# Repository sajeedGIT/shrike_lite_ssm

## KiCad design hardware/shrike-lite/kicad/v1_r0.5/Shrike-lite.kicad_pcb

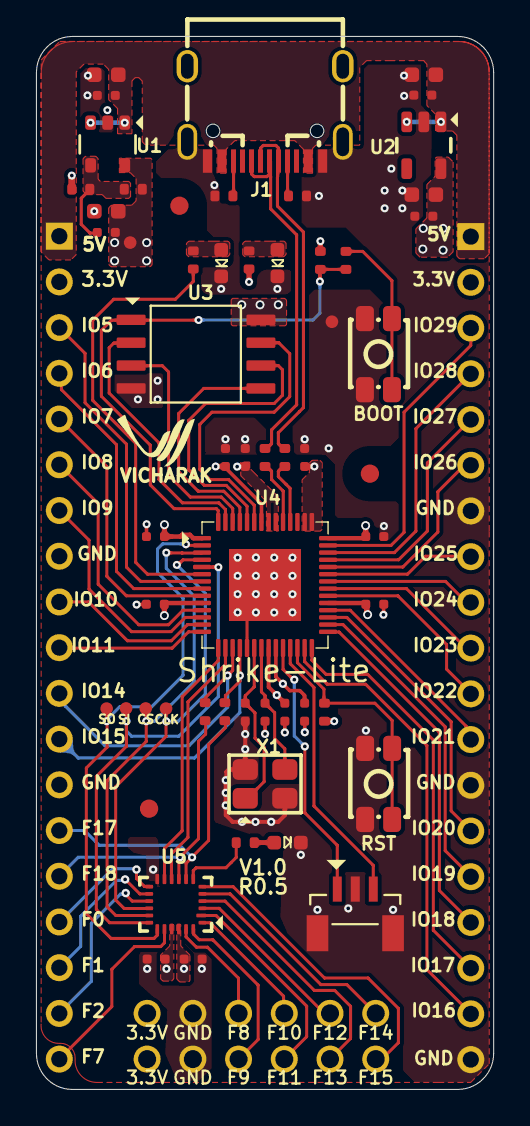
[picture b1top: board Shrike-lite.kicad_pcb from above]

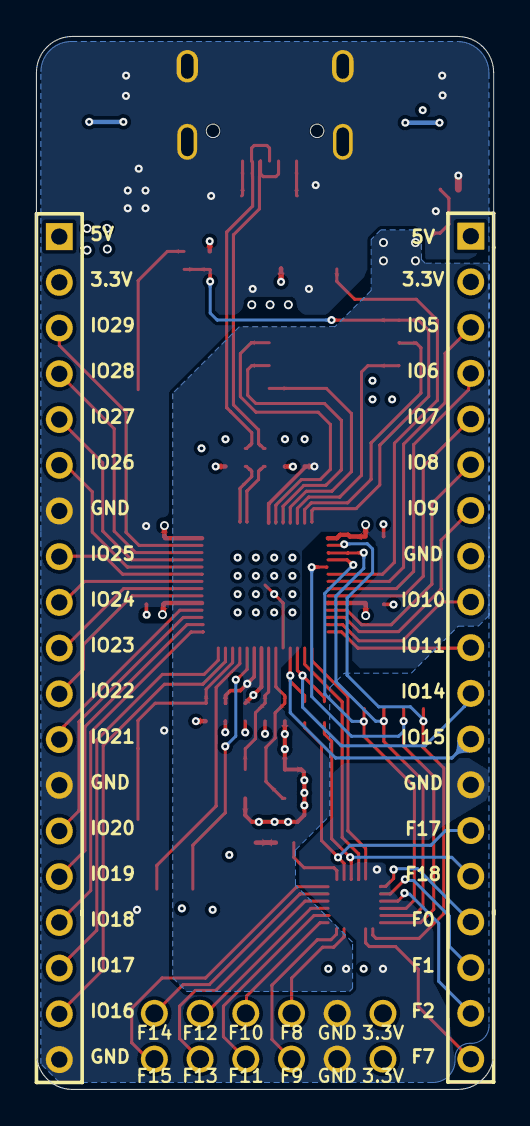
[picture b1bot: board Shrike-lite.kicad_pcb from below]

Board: 4 copper layers, 25.4 x 58.5 mm, 57 parts (2 on the bottom side), 71 nets.

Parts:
2: TP
C1, C3, C5, C8: 100nF 10V; Cap_0603
C2, C4, C6, C7, C9, C10, C11, C12, C13, C14, C15, C16, C17, C18, C19, C20, C21: Cap_0402
CLK: TP
CS: TP
D1: LED1; LED_0603
D2, D3: LED_0603
GND1: TP
J1: Type-C
J2, J4: Header 19X1_2.54MM; 1X19_HEADER
J3: DNP; 2X6_HEADER
J5: XUNPU WAFER-SH1.0-3PLB
R1: RES_0402_5; Res_0402
R2, R3, R4, R5, R6, R7, R8, R9, R10, R11, R12, R13, R14: Res_0402
SI: TP
SO: TP
SW1: SW PUSHBUTTON; SW_MICRO PUSH BUTTON 4 PAD
SW2: SW PUSHBUTTON; Switch
U1: SOT23-5
U2: SOT25
U3: SOIC-8
U4: RP2040; QFN_56
U5: QFN_24
X1: CRYSTAL_3225

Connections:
1.1V: 2.1, C7.2, C8.2, C11.1, C12.1, C20.1, R4.1, U1.5, U4.23, U4.50, U5.22
3.3V: C3.2, C4.2, C13.1, C14.1, C15.1, C16.1, C17.1, C18.1, C19.1, C21.1, J2.2, J3.1, J3.2, J4.2, R1.1, R9.1, R10.2, U2.5, U3.8, U4.1, U4.10, U4.22, U4.33, U4.42, U4.43, U4.44, U4.48, U4.49, U5.21
BOOT: R11.2, SW2.1, SW2.2
CS0: R9.2, R11.1, U3.1, U4.56
CS1: CS.1, U4.3, U5.17
EN: U4.16, U5.10
F_GPIO0: J2.16, U5.13
F_GPIO1: J2.17, U5.14
F_GPIO2: J2.18, U5.15
F_GPIO7: J2.19, U5.20
F_GPIO8: J3.6, U5.23
F_GPIO9: J3.5, U5.24
F_GPIO10: J3.8, U5.1
F_GPIO11: J3.7, U5.2
F_GPIO12: J3.10, U5.3
F_GPIO13: J3.9, U5.4
F_GPIO14: J3.12, U5.5
F_GPIO15: J3.11, U5.6
F_GPIO16: R6.1, U5.7
F_GPIO17: J2.14, R8.2, U5.8
F_GPIO18: J2.15, R7.2, U5.9
F_SPI_CLK: CLK.1, U4.4, U5.16
F_SPI_SI: SI.1, U4.5, U5.18
F_SPI_SO: SO.1, U4.2, U5.19
GND: C1.1, C2.1, C3.1, C4.1, C5.1, C6.1, C8.1, C9.2, C10.2, C11.2, C12.2, C13.2, C14.2, C15.2, C16.2, C17.2, C18.2, C19.2, C20.2, C21.2, D1.K, D2.K, D3.K, GND1.1, J1.A1, J1.A12, J1.S1, J1.S2, J1.S3, J1.S4, J2.8, J2.13, J3.3, J3.4, J4.7, J4.13, J4.19, J5.2, J5.4, J5.5, R2.2, R3.2, R5.2, SW1.3, SW1.4, SW2.3, SW2.4, U1.2, U2.2, U3.4, U4.19, U4.57, U5.12, X1.2, X1.4
GPIO4: R14.1, U4.6
GPIO5: J2.3, U4.7
GPIO6: J2.4, U4.8
GPIO7: J2.5, U4.9
GPIO8: J2.6, U4.11
GPIO9: J2.7, U4.12
GPIO10: J2.9, U4.13
GPIO11: J2.10, U4.14
GPIO14: J2.11, R7.1, U4.17
GPIO15: J2.12, R8.1, U4.18
GPIO16: J4.18, U4.27
GPIO17: J4.17, U4.28
GPIO18: J4.16, U4.29
GPIO19: J4.15, U4.30
GPIO20: J4.14, U4.31
GPIO21: J4.12, U4.32
GPIO22: J4.11, U4.34
GPIO23: J4.10, U4.35
GPIO24: J4.9, U4.36
GPIO25: J4.8, U4.37
GPIO26: J4.6, U4.38
GPIO27: J4.5, U4.39
GPIO28: J4.4, U4.40
GPIO29: J4.3, U4.41
HOLD: U3.7, U4.51
NetC7_1: C7.1, R4.2, R5.1, U1.4
NetD1_A: D1.A, R1.2
NetD2_A: D2.A, R6.2
NetD3_A: D3.A, R14.2
NetJ1_A5: J1.A5, R3.1
NetJ1_B5: J1.B5, R2.1
PWR: U4.15, U5.11
RUN: R10.1, SW1.1, SW1.2, U4.26
SPI_CLK: U3.6, U4.52
SPI_SI: U3.5, U4.53
SPI_SO: U3.2, U4.55
SWCLK: J5.1, U4.24
SWD: J5.3, U4.25
USB_N: J1.A7, J1.B7, R12.1
USB_P: J1.A6, J1.B6, R13.1
USBx_N: R12.2, U4.46
USBx_P: R13.2, U4.47
VUSB: C1.2, C2.2, C5.2, C6.2, J1.A4, J1.A9, J2.1, J4.1, U1.1, U1.3, U2.1, U2.3
WP: U3.3, U4.54
XIN: C9.1, U4.20, X1.1
XOUT: C10.1, U4.21, X1.3

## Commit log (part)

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2026-06-22 half adder
2026-06-22 full adder
